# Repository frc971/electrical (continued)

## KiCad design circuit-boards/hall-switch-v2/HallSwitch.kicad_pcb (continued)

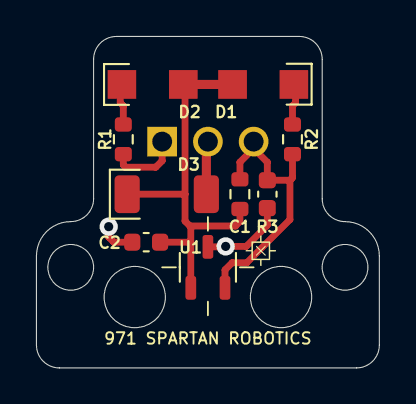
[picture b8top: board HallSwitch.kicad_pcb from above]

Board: 2 copper layers, 19.1 x 18.4 mm, 12 parts (1 on the bottom side), 6 nets.

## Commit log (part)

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2023-12-22 Initial creation of the NX-J401-Adapter board"
2023-12-22 "Adding readme and license to repo"
2023-12-23 Posting 2023 robot schematic
2023-12-23 Move NX-J401-Adapter PCB to new location under PCBs
2023-12-23 Adding NX-IndicatorBoard to repo
2023-12-23 Adding IMU-2x to the repo. NOTE: Switch footprints are bad.
2023-12-23 Adding IMU-2X-v2 fixes switch footprint.
2023-12-23 Add RPI power boards to repo from 971-Robot-Code
2023-12-23 Moving connector_boards, hall-effect, led-ring-driver, and RspPiPicoIMU
2023-12-23 Adding MIPI to HDMI board to repo
2023-12-23 Add beam break board to repo
2023-12-23 Adding power distribution fuse block
2023-12-23 Add Driver Station ButtonBoard2 to repo.
2023-12-23 Changed PCBs to circuit-boards
2023-12-25 Adding IMU-2X v3 which adds rate and heading PWM outputs
2023-12-25 Adding IMU-2X-v3/IMU-2X.kicad_prl
2023-12-26 Add NX-J401-Adapter V2. INCOMPLETE Requires fan connector.
2023-12-26 Added debug harness pinout
2023-12-28 Modified to expand M.2 adapter space, temp sensor connector and pwr LED
2023-12-29 Adding kraken power and can adapters
2023-12-31 Modified kraken power to rotate andersons 90 deg
2024-01-02 Increased clearance around key on kraken power adapter
2024-01-02 Increased board area to allow room for VHB between can and power boards.
2024-01-06 Adding NX Button Interface
2024-01-06 Add NX Button Interface Board
2024-01-07 Change SL connectors to surface mount solder wires.
2024-01-08 Added some part numbers
2024-01-11 Adding 2024 System Diagram skeleton
2024-01-11 Removing system drawing kicad backups and add .gitignore for backups
2024-01-13 Add PD fuse and Orin NX symbols
2024-01-15 Add wire tag to use instead of cable symbol.
2024-01-16 Adding initial system drawing that include motors
2024-01-20 Fixing bom and created gerbers for beam break board
2024-01-21 Updated boms and exported output files for connector boards
2024-01-21 System diagram update. Initial wiring complete
2024-01-25 Fixed system drawing
2024-01-25 Changed CAN ref des to number greater than 100 to allow future change
2024-01-27 Updated system drawing
2024-01-29 Adding CAN Terminator board
2024-01-29 Updated the motor can bus assignments
2024-02-03 Update the CAN-FD bus wiring
2024-02-03 Adding updated system drawing schematic and pdf
2024-02-03 Adding beambreak ibom
2024-02-04 Cleaned up system drawing
2024-02-04 Adding RPI-PowerBoard output files
2024-02-12 Minor mods to sys drawing
2024-02-12 Add driver station button connector board
2024-02-12 Added driver camera to system drawing
2024-02-15 Modified sys dwg rio ethernet, added comment to nx adapter
2024-02-15 Updated gitignore
2024-02-15 Update gitignore for kicad files
2024-02-17 Move right side motor PDB connections
2024-02-18 sat feb 17 system diagram
2024-02-18 Update system diagram can bus
2024-02-18 Change Note Retiontion to Note Hold
2024-02-19 Updating system diagram to reflect the robot wiring
2024-02-20 Adding CAN FD IDs to sys drawing
2024-02-22 Add can ids for remaining motors
2024-02-22 Adding 20203 Driver Station schematic
2024-02-24 Change transfer roller beam break circuit to DNP
2024-02-24 Swapped Dump and Extend inputs to PDB on system dwg
2024-02-24 Move Candle to VRM2 in sys dwg
2024-02-26 Sys dwg: Swap right and left robot, move alt and catapult motors to FD
2024-02-27 DNP third Orin-NX and move IMU to 2nd Orin
2024-03-01 Moved extend to CAN-FD. Added NX to CAN-FD bus
2024-03-01 Assigned cameras to the NX modules
2024-03-01 Removing NX from Kraken bus due to CAN-FD conflict
2024-03-02 Swapped turret with extend and transfer rollers to move extend to 40A
2024-03-17 Update sys diag. IMU CAN radio pwr
2024-03-24 Marked NX indicator pull-down res as DNP to work with interface bd.
2024-06-09 "Initial check-in of CNC Router ESTOP circuit"
2024-06-16 Update CNC router to as-built
2024-06-21 Sample Kraken Can V2
2024-06-22 Kraken Can V2
2024-06-22 Add Kraken Can Adapter V2
2024-06-22 Fixed kraken-can-adapter V2.
2024-06-22 Adding kraken-can-adapter-V2 increases connector retention
2024-06-23 CAN Adapter - Adjusted the connector clearance
2024-06-30 ButtonBd2 - Change connectors to gold plate. Add headers for teensy
2024-07-06 Add circuit board readme from AlexL
2024-07-06 Minor fixes to the circuit board readme
2024-07-06 Minor fix to README
2024-07-14 Initial checkin
2024-07-14 Moved LED connector to clear lower board
2024-07-15 Add item increment to kicad-export-fab.sh bom export
2024-07-16 Initial check-in of NX Adapter board v3
2024-07-19 Interim checkin of NX Adapter board
2024-07-20 NX Adapter interim checking
2024-07-22 Check in of NX Adapter and Indicator boards. Complete pending review
2024-07-28 Intermediate checkin of NX-Indicator-board
2024-07-29 Checkin of NX Indicator board 2x CAN FD + 6 LEDs
2024-07-29 Checkin of NX J401 Adapter-V3 Moved mounting holes to match indicator bd
2024-07-30 Initial checkin of kraken pwm controller
2024-08-05 Minor update to NX-J401-Adapter-v3
2024-08-05 Fix bom. Made LVC245 an SO-20 part
2024-08-05 Minor BOM fix
2024-08-09 Changed NX-adapter diff pairs to non-coplaner wave guide
2024-08-10 Updated diff pairs and power supply layout
2024-08-11 minor update to boost converter layout
2024-08-11 Checkin of NX-Button Interface V2
2024-08-17 Add NX Button Interface V2
2024-08-18 Add ground vias near diff pair vias to improve signal integrity.
2024-08-19 Add R2 of Hall Switch
2024-08-19 Add r2 of hallswitch
2024-08-21 initial checkin of mag encoder.
2024-08-22 Add SPI header for config. Center mounting holes on sensor
2024-08-24 Checking in 2 options of mag-encoder. WIP
2024-08-25 checkin of mag encoder
2024-08-25 removing directory for mag-encoder3
2024-08-26 changed pins to 0.125". Changed OK LED driver to mosfet.
2024-08-31 Commit for mag-encoder2 with to fit within 1.25" bearing race
2024-08-31 Changed power LED to yellow. Reverse polarity diode to 1N4148
2024-09-08 Adding kicad export scripts
2024-09-14 Update the IMU-2X design files ot new kicad rev. Assy files etc.
2024-09-21 Add PDBv2, HallSwitchv2 and TeeCan
2024-09-28 Export files for new pcbs + board characteristics
2024-10-08 Add new boms (gold-plated tee-can)etc
2024-10-12 Fix pcb fab layers
2024-10-12 Minor Fab fixes
2024-10-15 Checking in Hall Switch Gerbers
2024-10-15 Updating Power Distribution Board V2 Output Files
2024-10-15 Adding TEE-CAN-SL Output files
2024-10-18 Add thermal relief for resistors
2024-10-19 Add ibom for Power Distribution Board
2024-10-19 WIP checkin of swerve controller harness
2024-10-25 Revised mag encoder based on WP feedback
2024-11-11 Add CAN transceiver to button interface
2024-11-25 Add mag encoder V4 to add fault handling
2024-11-26 Minor layout fix to mag encoder
2024-12-04 Change Green LED current to 5mA
2024-12-07 Update mag encoder silk and board color
